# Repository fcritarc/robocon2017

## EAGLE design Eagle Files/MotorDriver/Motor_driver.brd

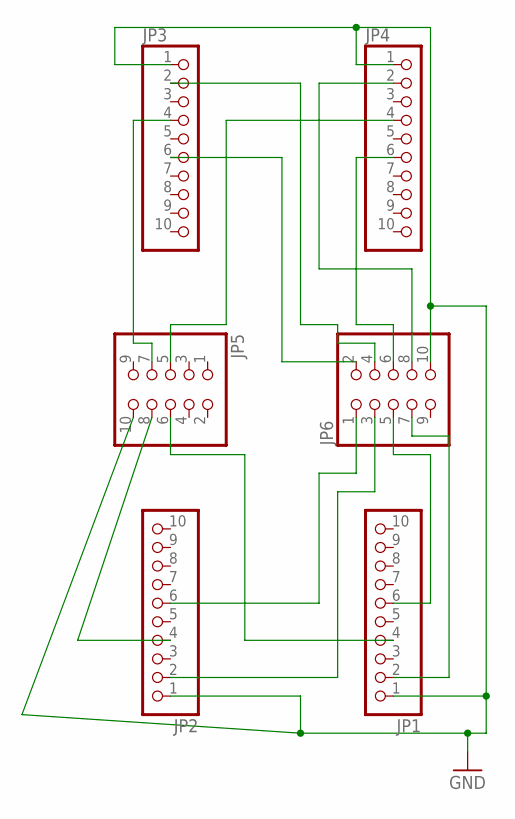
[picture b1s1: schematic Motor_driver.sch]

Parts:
JP1, JP2, JP3, JP4: PINHD-1X10; 1X10
JP5, JP6: PINHD-2X5; 2X05

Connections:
GND: JP1.1, JP2.1, JP3.1, JP4.1, JP5.10, JP6.10
unnamed: JP4.2, JP6.8
unnamed: JP4.6, JP6.6
unnamed: JP1.6, JP6.5
unnamed: JP1.2, JP6.7
unnamed: JP3.2, JP6.4
unnamed: JP3.6, JP6.2
unnamed: JP2.2, JP6.3
unnamed: JP2.6, JP6.1
unnamed: JP4.4, JP5.5
unnamed: JP3.4, JP5.7
unnamed: JP1.4, JP5.6
unnamed: JP2.4, JP5.8

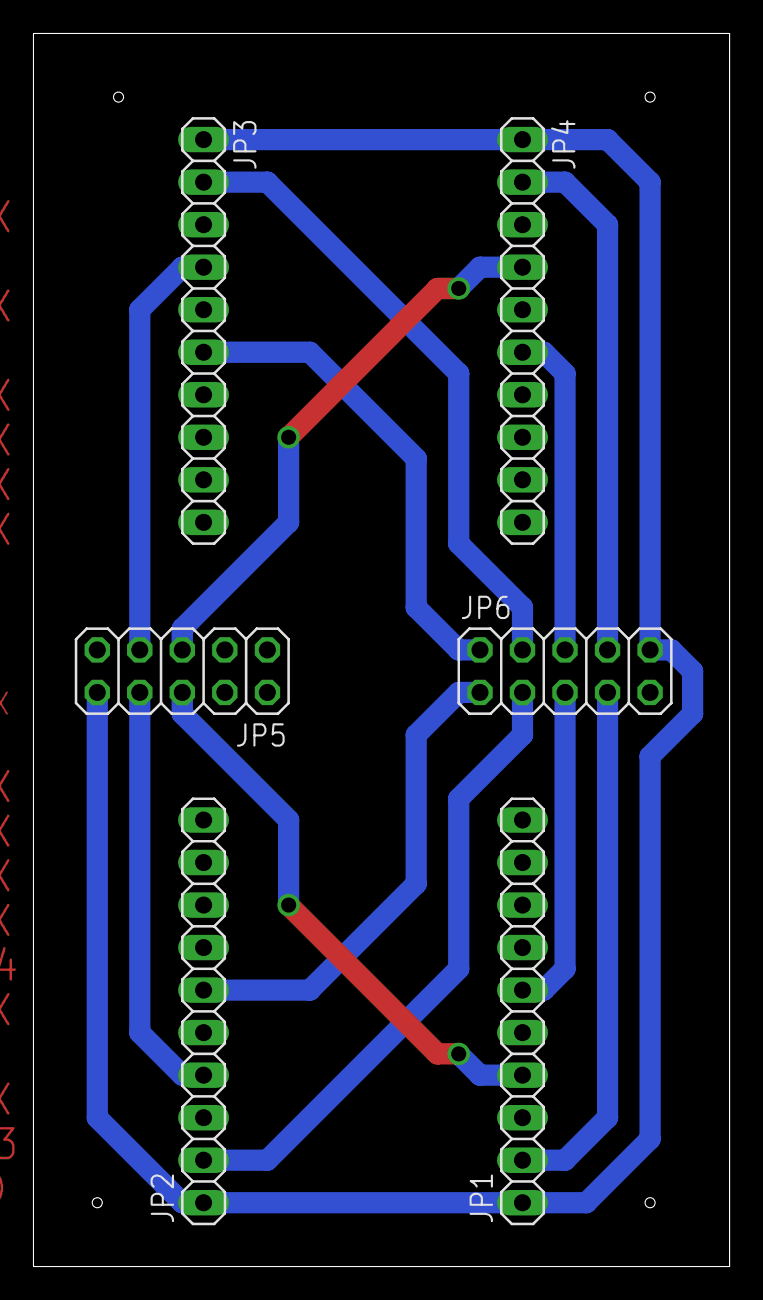
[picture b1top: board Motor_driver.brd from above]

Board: 2 copper layers, 41.6 x 73.7 mm, 6 parts (0 on the bottom side), 13 nets.

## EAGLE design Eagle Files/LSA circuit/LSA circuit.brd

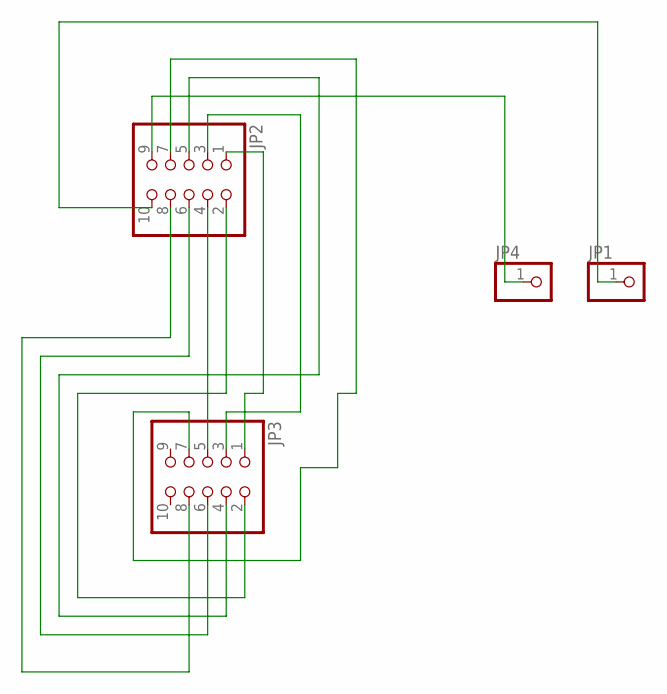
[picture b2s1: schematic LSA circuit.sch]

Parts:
JP1, JP4: PINHD-1X1; 1X01
JP2, JP3: PINHD-2X5; 2X05

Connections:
unnamed: JP2.9, JP4.1
unnamed: JP1.1, JP2.10
unnamed: JP2.1, JP3.1
unnamed: JP2.2, JP3.2
unnamed: JP2.4, JP3.4
unnamed: JP2.6, JP3.6
unnamed: JP2.8, JP3.8
unnamed: JP2.3, JP3.3
unnamed: JP2.5, JP3.5
unnamed: JP2.7, JP3.7

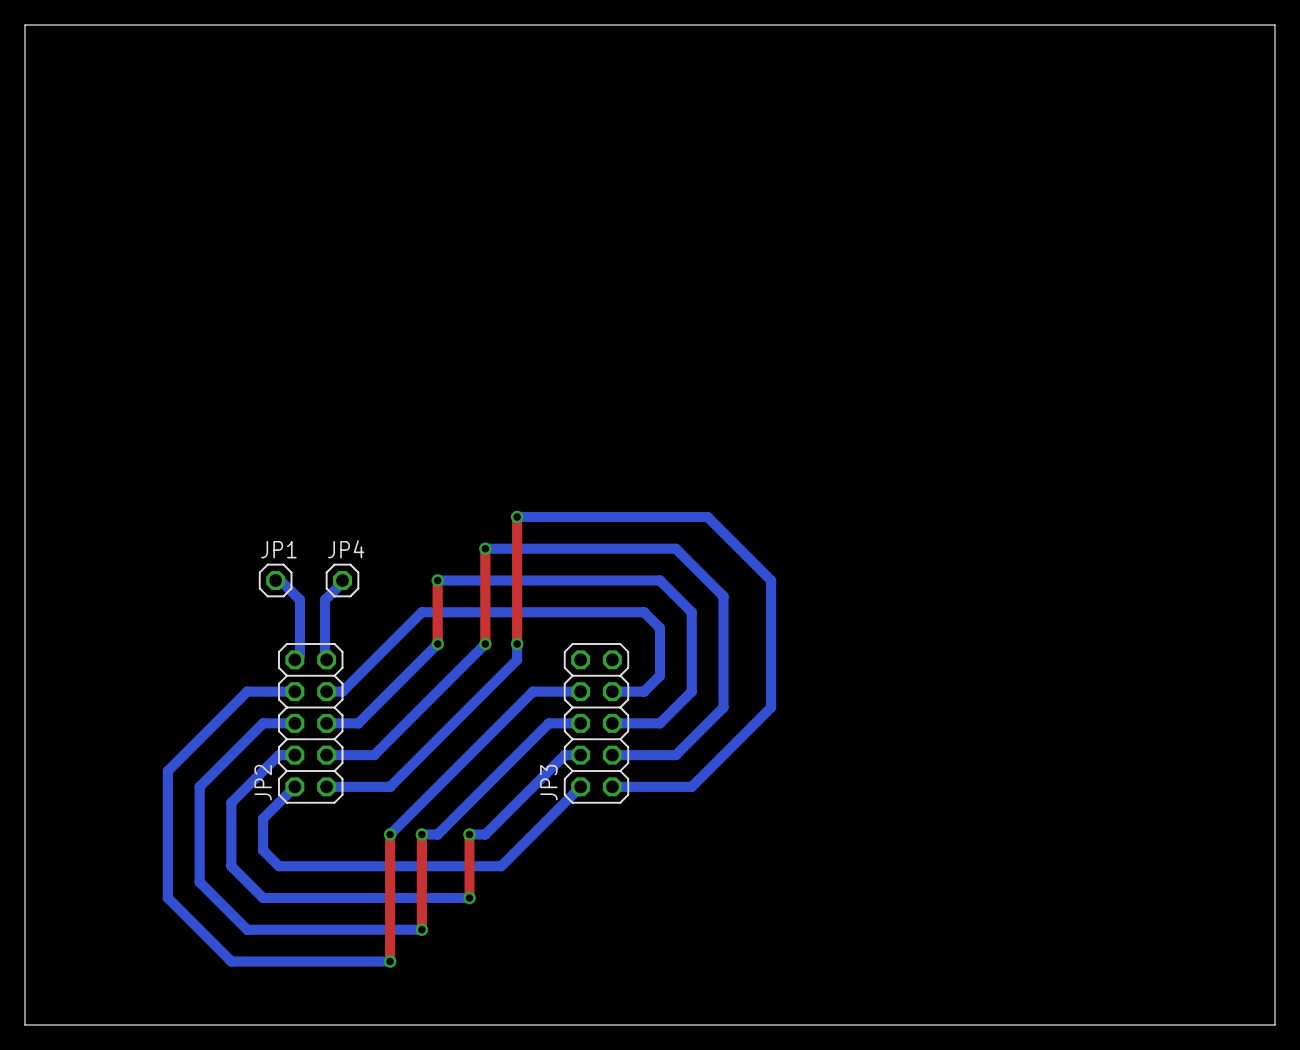
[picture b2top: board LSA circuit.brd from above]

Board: 2 copper layers, 100.0 x 80.0 mm, 4 parts (0 on the bottom side), 10 nets.

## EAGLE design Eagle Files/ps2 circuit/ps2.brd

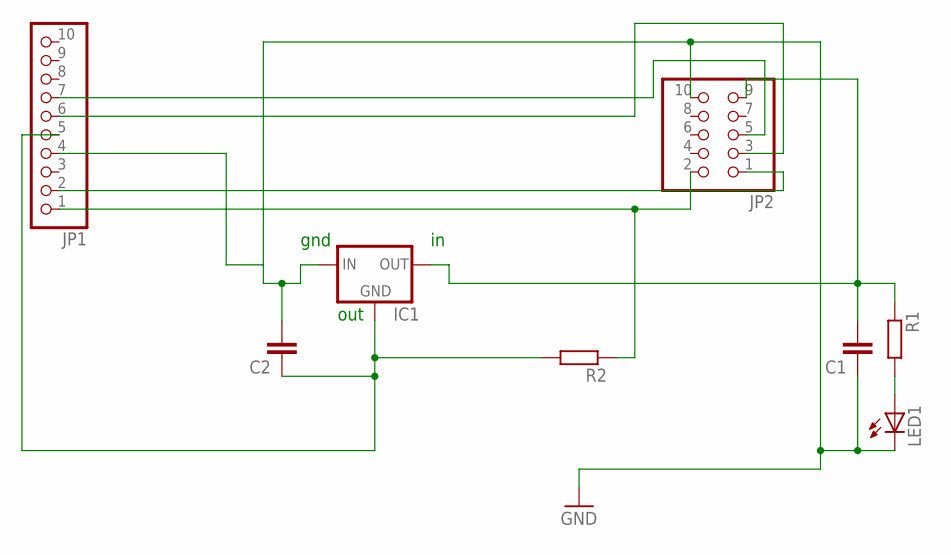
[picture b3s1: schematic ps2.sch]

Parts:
C1, C2: C2,5-3; C2.5-3
IC1: 78MXXS
JP1: PINHD-1X10; 1X10
JP2: PINHD-2X5; 2X05
LED1: LED3MM
R1, R2: R-EU_0207/10; 0207/10

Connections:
GND: C1.1, C2.2, IC1.IN, JP1.4, JP2.10, LED1.K (C)
unnamed: JP1.1, JP2.2, R2.1
unnamed: JP1.2, JP2.1
unnamed: JP1.6, JP2.3
unnamed: JP1.7, JP2.5
unnamed: C2.1, IC1.GND, JP1.5, R2.2
unnamed: C1.2, IC1.OUT, JP2.9, R1.1
unnamed: LED1.A, R1.2

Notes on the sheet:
gnd
out

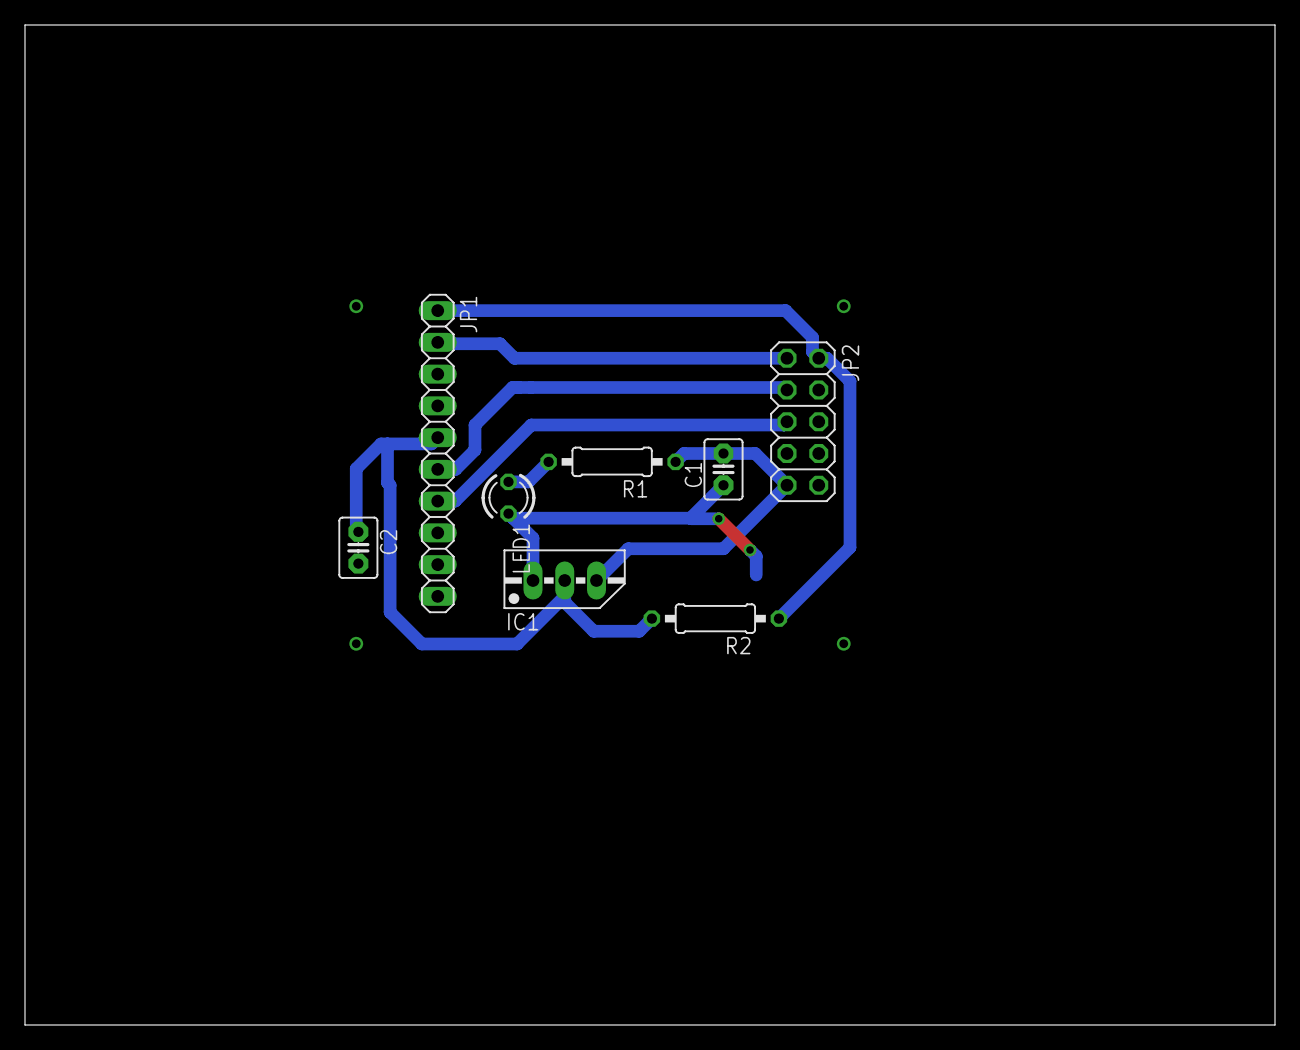
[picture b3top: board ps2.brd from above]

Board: 2 copper layers, 100.0 x 80.0 mm, 8 parts (0 on the bottom side), 8 nets.

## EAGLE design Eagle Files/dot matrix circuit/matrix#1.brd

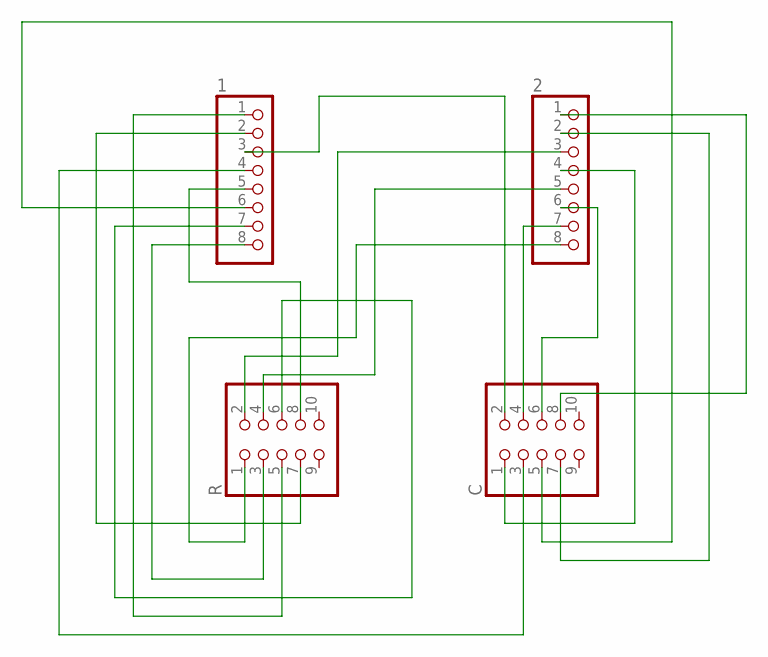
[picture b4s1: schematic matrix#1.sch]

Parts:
1, 2: PINHD-1X8; 1X08
C: PINHD-2X5; 2X05
R: PINHD-2X5; 2X05

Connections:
unnamed: 2.8, R.1
unnamed: 2.3, R.2
unnamed: 1.8, R.3
unnamed: 2.5, R.4
unnamed: 1.1, R.5
unnamed: 1.7, R.6
unnamed: 1.2, R.7
unnamed: 1.5, R.8
unnamed: 2.4, C.1
unnamed: 1.3, C.2
unnamed: 1.4, C.3
unnamed: 2.7, C.4
unnamed: 1.6, C.5
unnamed: 2.6, C.6
unnamed: 2.2, C.7
unnamed: 2.1, C.8

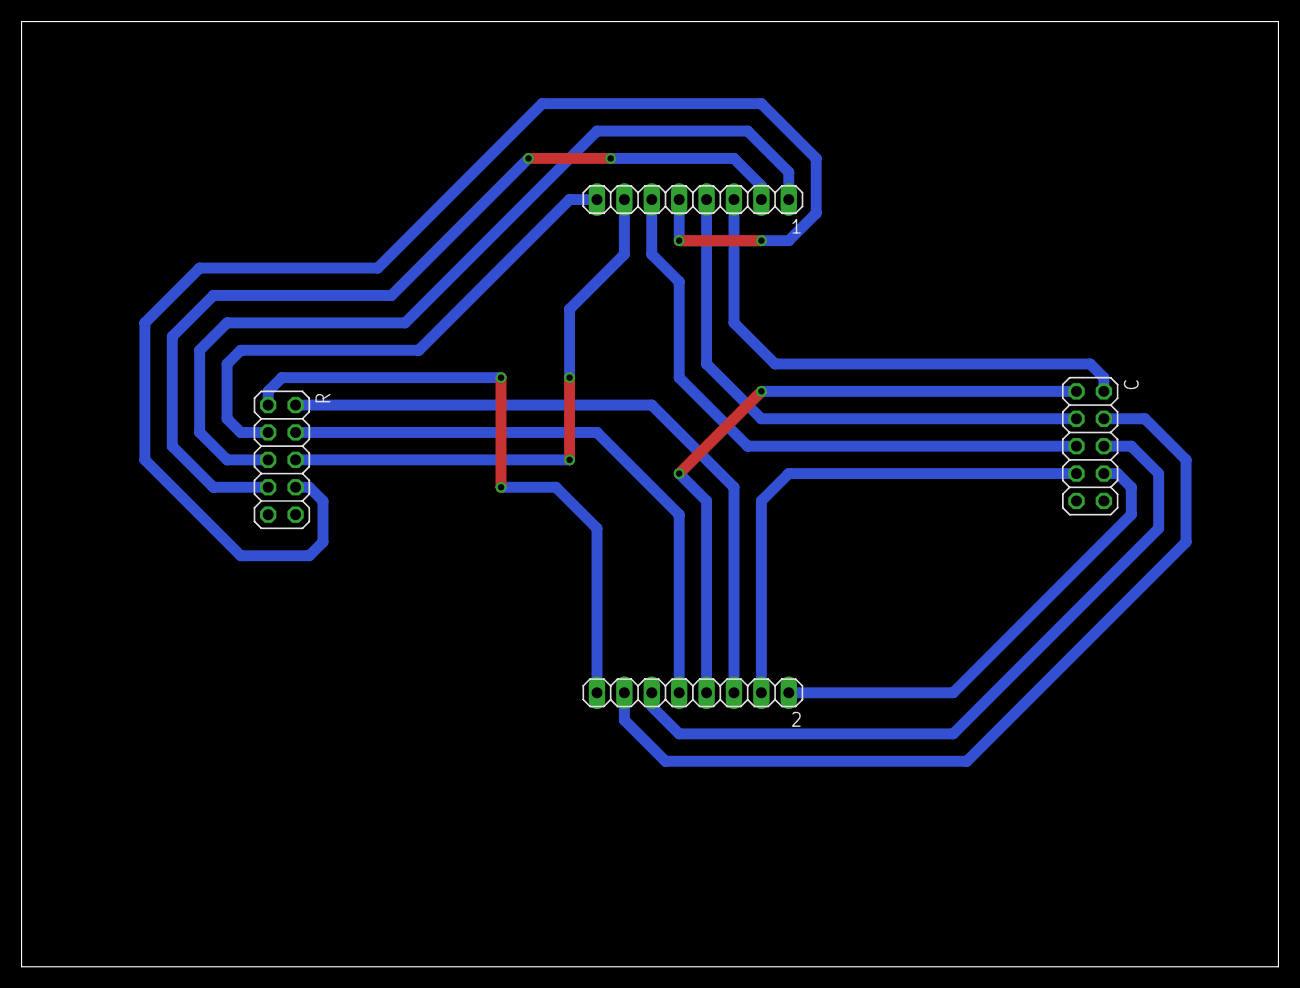
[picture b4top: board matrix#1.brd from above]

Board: 2 copper layers, 116.5 x 87.6 mm, 4 parts (0 on the bottom side), 16 nets.

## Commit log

2016-11-18 readme added
2016-11-18 readme added (#1)
2016-12-30 update 1
2017-01-01 commit 2
2017-01-04 eagle files added
2017-01-05 added motor driver eagle files
2017-01-22 added prototype_rev
